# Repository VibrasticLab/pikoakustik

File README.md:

This is audiometri tool project (still in heavy development).
Main chip are STM32F401RE and Audio-DAC MAX98357A.

### Update:

After a year or so development struggle, now we move to some higher level development stage.
Therefor this repository will be archived and exist only for documentation.

Next development will be moved into new repository: [Pikoakustik2](https://github.com/VibrasticLab/pikoakustik2)

---

### Short Description:

- [x] Fungsional

Mengukur Ambang Pendengaran secara mandiri tanpa perlu bantuan dokter spesialis dan tanpa datang ke klinik.

- [x] Portabel

Dapat digunakan dimana saja dan kapan saja. Baterai mudah diisi ulang.

- [x] Terstandar

Telah terkalibrasi standar Audiometri dan teruji pada ruang *un-echoic*.

- [x] Ramah Pengguna

Antar Muka hanya berupa Tombol dan Lampu LED tanpa pengaturan tambahan dan bisa langsung digunakan.

- [x] Terintergrasi

Terhubung dengan penyimpanan *dedicated server* sehingga dapat diakses dokter spesialis secara jarak jauh jika diperlukan.

---

### Marking Rules:
- [ ] Unfinished
- [x] Finished but Open to Improve
- [x] ~~Finished~~
- [ ] ~~Unused but Noted~~

---

### Implemented Features:

#### User Interaction:

- [X] ~~LED Run Mode Indicator~~
	- [x] ~~Measurement Mode: Blink fast~~
	- [x] ~~Idle Mode: Blink slow~~
	- [x] ~~No Media Mode: Blink fast every 2s~~
- [X] ~~LED TRUE/FALSE~~
- [X] ~~LED Play/MMC~~
- [x] ~~LED 3 Choices~~
- [X] ~~Button Choices~~
	- [x] ~~3 Button Choices~~
	- [x] 3 Choices Random Generator
	- [x] ~~3 Choice Answer Placement~~
- [x] ~~Button Reset~~
- [x] ~~User-Friendlyness Interface Test~~
- [ ] LCD Non-Input Interface
	- [ ] LCD SPI ILI9xxx series

---

#### Packaging

- [x] ~~Acrilic Protector~~
- [ ] Box Design
	- [x] Print 3D
	- [ ] Plastic Molding
	- [x] Brosur Promo with Good Packaging
- [ ] Battery
	- [x] Regulator TP4056
	- [x] ~~LiPo Battery~~
	- [x] ~~Main Power Button~~
	- [ ] Charge/Discharge Test
	- [ ] Battery Manager
	- [x] No Cap except Run Elco

---

#### Data Communication:

- [ ] Serial Data
	- [x] ~~ACM USB-CDC Protocol~~
	- [x] ~~Basic Serial commands~~
	- [x] ~~Media handling commands~~
	- [x] ~~Audiometri control commands~~
	- [ ] HTTP Data control commands

- [x] ~~Media Storage~~
	- [x] ~~MMC Connector Slot~~
	- [x] ~~MMC readyness checking~~
	- [x] ~~FATFS as FAT32 handler~~
	- [x] ~~Via SPI protocol~~

- [ ] IoT Exchanges
	- [x] ESP-12E slot on PCB
	- [x] ESP-12E power jumper
	- [x] WiFi handling
	- [x] Access Point handling
	- [ ] Wifi/AP switch command
	- [ ] HTTP Data exchange
	- [ ] HTTP Data JSON/Format

---

#### Audiometri:

- [ ] Tone Generator
	- [x] ~~Generic I2S Protocol~~
	- [x] ~~Pure Single Tone~~
	- [x] Calibrated Frequency array
	- [x] Pop-Click Suppression
	- [x] Calibrated SPL range
	- [x] Calibrated SPL scaling
	- [x] Left/Right Isolation
	- [ ] Number Headphones
		- [ ] Embedded Tone Model
		- [ ] External Tone Model

- [ ] Hearing Test
	- [x] User Test Flow
	- [ ] **Convinient Level Test**
	- [ ] Random starting SPL
	- [x] Up/Down SPL scaling
	- [ ] Lowest Tone still too loud
	- [ ] Suffle Block
		- [ ] 1 Block is 1 Freq in 1 Channel
		- [ ] Left/Right suffle

- [ ] Microphone Input
	- [ ] Environment Noise Capture
	- [ ] Environment Noise Compensation

- [ ] Mass Production
	- [ ] PCB Electronic
		- [ ] Seeed Studio
		- [ ] ~~DigiKey~~
		- [ ] Xirca
		- [ ] Gerai-Cerdas
		- [ ] ~~Maxtron~~
	- [ ] Packaging

---

### Future Development:

- [ ] Migrate to ESP32
	- [ ] Advantage: Bluetooth Audio A2DP Sources
	- [ ] Advantage: Dual Core CPU as fast as ARM
	- [ ] Advantage: Touch Sensor (replace button)
	- [ ] Disadvantage: Less GPIO pin available
	- [ ] Disadvantage: Re-working all current design
	- [ ] Disadvantage: Re-calibrate and re-test everything

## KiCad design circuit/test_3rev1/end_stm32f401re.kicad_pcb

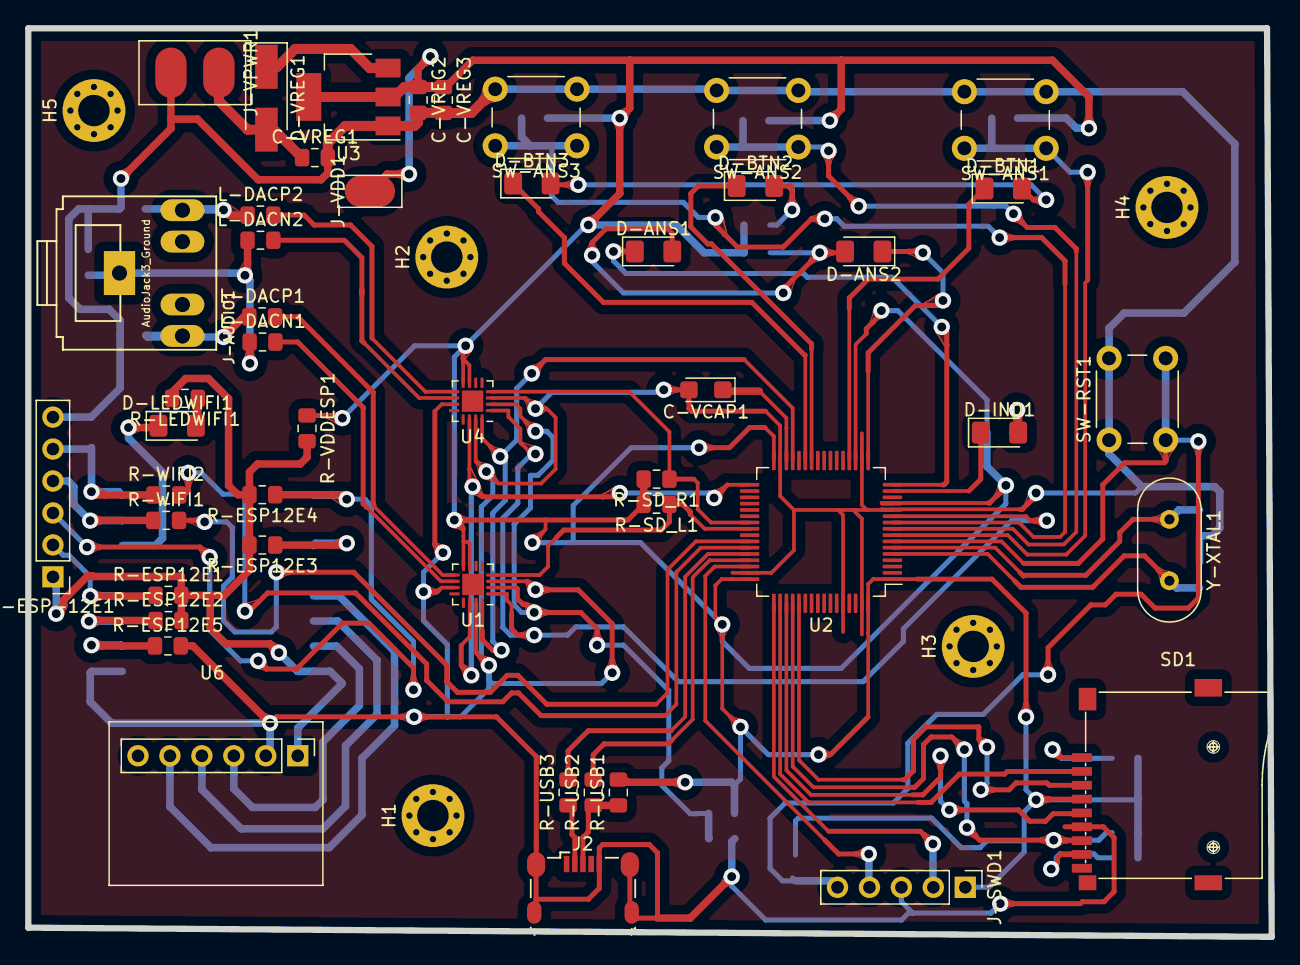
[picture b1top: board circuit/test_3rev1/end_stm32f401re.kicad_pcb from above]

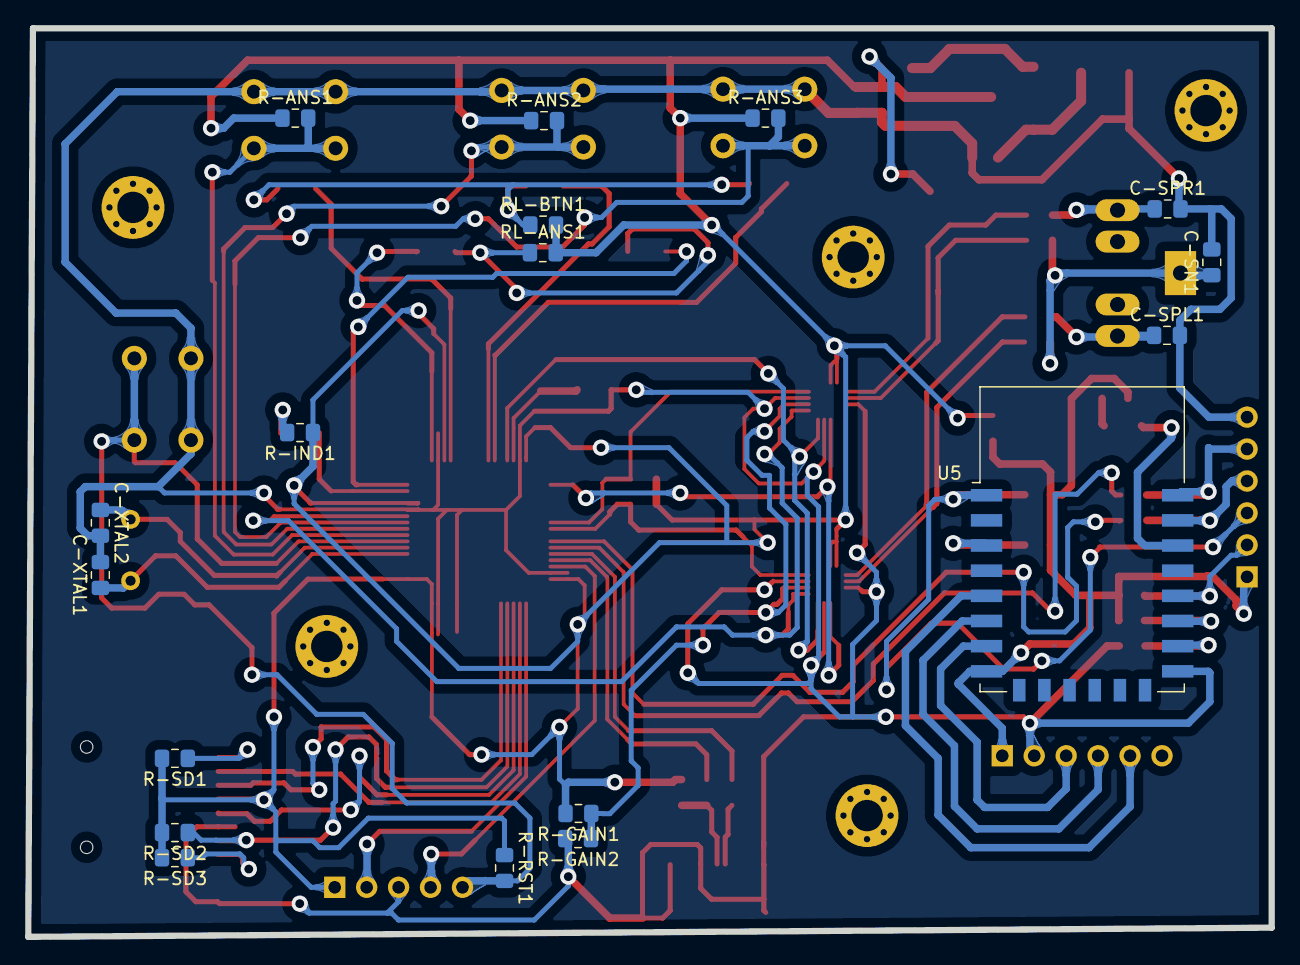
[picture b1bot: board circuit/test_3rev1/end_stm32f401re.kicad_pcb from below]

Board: 2 copper layers, 98.9 x 72.2 mm, 70 parts (18 on the bottom side), 60 nets.

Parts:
C-SN1: 220pF; C_0805_2012Metric_Pad1.15x1.40mm_HandSolder
C-SPL1: 220pF; C_0805_2012Metric_Pad1.15x1.40mm_HandSolder
C-SPR1: 220pF; C_0805_2012Metric_Pad1.15x1.40mm_HandSolder
C-VCAP1: 4.7uF; CP_EIA-3216-18_Kemet-A
C-VREG1, C-VREG2, C-VREG3: C; C_0805_2012Metric_Pad1.15x1.40mm_HandSolder
C-XTAL1, C-XTAL2: C; C_0805_2012Metric_Pad1.15x1.40mm_HandSolder
D-ANS1, D-ANS2: LED; LED_1206_3216Metric_Pad1.42x1.75mm_HandSolder
D-BTN1, D-BTN2, D-BTN3: LED; LED_1206_3216Metric_Pad1.42x1.75mm_HandSolder
D-IND1: LED; LED_1206_3216Metric_Pad1.42x1.75mm_HandSolder
D-LEDWIFI1: LED; LED_1206_3216Metric_Pad1.42x1.75mm_HandSolder
D-VREG1: D; D_SMA_Handsoldering
H1, H2, H3, H4: MountingHole; MountingHole_2.5mm_Pad_Via
H5: CableHole; MountingHole_2.5mm_Pad_Via
J2: USB_B_Micro; MicroUSB
J-AUDIO1: AudioJack3_Ground; Tayda_3.5mm_stereo_TRS_jack_A-853
J-ESP-12E1: Conn_01x06_Male; PinHeader_1x06_P2.54mm_Vertical
J-SWD1: Conn_01x05_Male; PinHeader_1x05_P2.54mm_Vertical
J-VDD1: Conn_01x01_Male; vpin-x1
J-VPWR1: Conn_01x02_Male; vpin-x2
L-DACN1, L-DACN2: 100uH; L_0805_2012Metric_Pad1.15x1.40mm_HandSolder
L-DACP1, L-DACP2: 100uH; L_0805_2012Metric_Pad1.15x1.40mm_HandSolder
R-ANS1, R-ANS2, R-ANS3: 10K; R_0805_2012Metric_Pad1.15x1.40mm_HandSolder
R-ESP12E1, R-ESP12E2, R-ESP12E3, R-ESP12E4, R-ESP12E5: 10K; R_0805_2012Metric_Pad1.15x1.40mm_HandSolder
R-GAIN1, R-GAIN2: 100K; R_0805_2012Metric_Pad1.15x1.40mm_HandSolder
R-IND1: 330; R_0805_2012Metric_Pad1.15x1.40mm_HandSolder
R-LEDWIFI1: 330; R_0805_2012Metric_Pad1.15x1.40mm_HandSolder
R-RST1: 10K; R_0805_2012Metric_Pad1.15x1.40mm_HandSolder
R-SD1, R-SD2, R-SD3: 10K; R_0805_2012Metric_Pad1.15x1.40mm_HandSolder
R-SD_L1: 1M; R_0805_2012Metric_Pad1.15x1.40mm_HandSolder
R-SD_R1: 1M; R_0805_2012Metric_Pad1.15x1.40mm_HandSolder
R-USB1: 4K7; R_0805_2012Metric_Pad1.15x1.40mm_HandSolder
R-USB2, R-USB3: 68; R_0805_2012Metric_Pad1.15x1.40mm_HandSolder
R-VDDESP1: 0; R_0805_2012Metric_Pad1.15x1.40mm_HandSolder
R-WIFI1, R-WIFI2: 0; R_0805_2012Metric_Pad1.15x1.40mm_HandSolder
RL-ANS1: 330; R_0805_2012Metric_Pad1.15x1.40mm_HandSolder
RL-BTN1: 330; R_0805_2012Metric_Pad1.15x1.40mm_HandSolder
SD1: MICRO-SD-CARD-SOCKET-9P_ST-TF-003A_; MICRO-SD9+4P-SMD-16.1X14.5X1.85MM
SW-ANS1, SW-ANS2, SW-ANS3: SW_Push; SW_PUSH_6mm
SW-RST1: SW_Push; SW_PUSH_6mm
U1, U4: MAX98357; QFN-16-1EP_3x3mm_P0.5mm_EP1.7x1.7mm
U2: STM32F401RETx; LQFP-64_10x10mm_P0.5mm
U3: AMS1117-3.3; SOT-223-3_TabPin2
U5: ESP-12E
U6: SPH0645; sph0645
Y-XTAL1: 16MHz; Crystal_HC49-4H_Vertical

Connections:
/BTN_A: R-ANS1.2, SW-ANS1.1, U2.8
/BTN_B: R-ANS2.2, SW-ANS2.1, U2.9
/BTN_C: R-ANS3.2, SW-ANS3.1, U2.10
/DAC_BCLK: U1.16, U2.29, U4.16
/DAC_DIN: U1.1, U2.11, U4.1
/DAC_GAIN: R-GAIN1.1, R-GAIN2.1, U1.2, U4.2
/DAC_LRC: U1.14, U2.33, U4.14
/DAC_L_SD: R-SD_L1.1, U1.4, U2.40
/DAC_R_SD: R-SD_R1.1, U2.39, U4.4
/ESP_EN: R-ESP12E3.1, U5.3
/ESP_LEDWIFI: D-LEDWIFI1.1, U5.20
/ESP_P0: J-ESP-12E1.2, R-ESP12E1.1, U5.18
/ESP_P2: R-ESP12E2.1, U5.17
/ESP_P15: R-ESP12E5.1, U5.16
/ESP_RST: J-ESP-12E1.3, R-ESP12E4.1, U5.1
/ESP_RXD: J-ESP-12E1.4, R-WIFI1.1, U5.21
/ESP_TXD: J-ESP-12E1.5, R-WIFI2.1, U5.22
/LED_A: D-BTN1.1, U2.20
/LED_B: D-BTN2.1, U2.26
/LED_C: D-BTN3.1, U2.27
/LED_FALSE: D-ANS2.1, U2.17
/LED_IND: D-IND1.1, U2.15
/LED_TRUE: D-ANS1.1, U2.16
/MIC_BCLK: U5.7, U6.3
/MIC_DOUT: U5.6, U6.4
/MIC_LRCL: U5.5, U6.5
/MMC_MISO: R-SD2.1, SD1.7, U2.52
/MMC_MOSI: SD1.3, U2.53
/MMC_NSS: SD1.2, U2.50
/MMC_SCK: SD1.5, U2.51
/NRST: J-SWD1.5, R-RST1.2, SW-RST1.2, U2.7
/OUTN: C-SN1.1, J-AUDIO1.S, L-DACN1.1, L-DACN2.1
/OUTP_L: C-SPL1.1, J-AUDIO1.T, L-DACP1.1
/OUTP_R: C-SPR1.1, J-AUDIO1.R, L-DACP2.1
/SW_CLK: J-SWD1.2, U2.49
/SW_DIO: J-SWD1.4, U2.46
/USB_DM: R-USB3.2, U2.44
/USB_DP: R-USB2.2, U2.45
/VDD-ESP8266: J-ESP-12E1.1, R-ESP12E1.2, R-ESP12E2.2, R-ESP12E3.2, R-ESP12E4.2, R-LEDWIFI1.2, R-VDDESP1.2, U5.8, U6.1
/WIFI_RXD: R-WIFI2.2, U2.43
/WIFI_TXD: R-WIFI1.2, U2.42
GND: C-SN1.2, C-SPL1.2, C-SPR1.2, C-VCAP1.2, C-VREG1.2, C-VREG2.2, C-VREG3.2, C-XTAL1.2, C-XTAL2.2, J2.5, J2.6, J-ESP-12E1.6, J-SWD1.3, J-VPWR1.2, R-ESP12E5.2, R-GAIN2.2, SD1.6, SW-ANS1.2, SW-ANS2.2, SW-ANS3.2, SW-RST1.1, U1.3, U1.11, U1.15, U2.12, U2.18, U2.31, U2.47, U2.60, U2.63, U3.1, U4.3, U4.11, U4.15, U5.15, U6.2
unnamed: C-VCAP1.1, U2.30
unnamed: C-XTAL1.1, U2.5, Y-XTAL1.2
unnamed: C-XTAL2.1, U2.6, Y-XTAL1.1
unnamed: D-ANS1.2, D-ANS2.2, RL-ANS1.1
unnamed: D-BTN1.2, D-BTN2.2, D-BTN3.2, RL-BTN1.1
unnamed: D-IND1.2, R-IND1.2
unnamed: D-LEDWIFI1.2, R-LEDWIFI1.1
unnamed: D-VREG1.1, U3.3
unnamed: J2.2, R-USB3.1
unnamed: J2.3, R-USB1.1, R-USB2.1
unnamed: L-DACN1.2, U1.10
unnamed: L-DACN2.2, U4.10
unnamed: L-DACP1.2, U1.9
unnamed: L-DACP2.2, U4.9
unnamed: R-SD1.1, SD1.1
unnamed: R-SD3.1, SD1.8
VCC: C-VREG1.1, D-VREG1.2, J-VPWR1.1
VDD: C-VREG2.1, C-VREG3.1, J-SWD1.1, J-VDD1.1, R-ANS1.1, R-ANS2.1, R-ANS3.1, R-GAIN1.2, R-IND1.1, R-RST1.1, R-SD1.2, R-SD2.2, R-SD3.2, R-SD_L1.2, R-SD_R1.2, R-USB1.2, R-VDDESP1.1, RL-ANS1.2, RL-BTN1.2, SD1.4, U1.7, U1.8, U2.1, U2.13, U2.19, U2.32, U2.48, U2.64, U3.2, U4.7, U4.8

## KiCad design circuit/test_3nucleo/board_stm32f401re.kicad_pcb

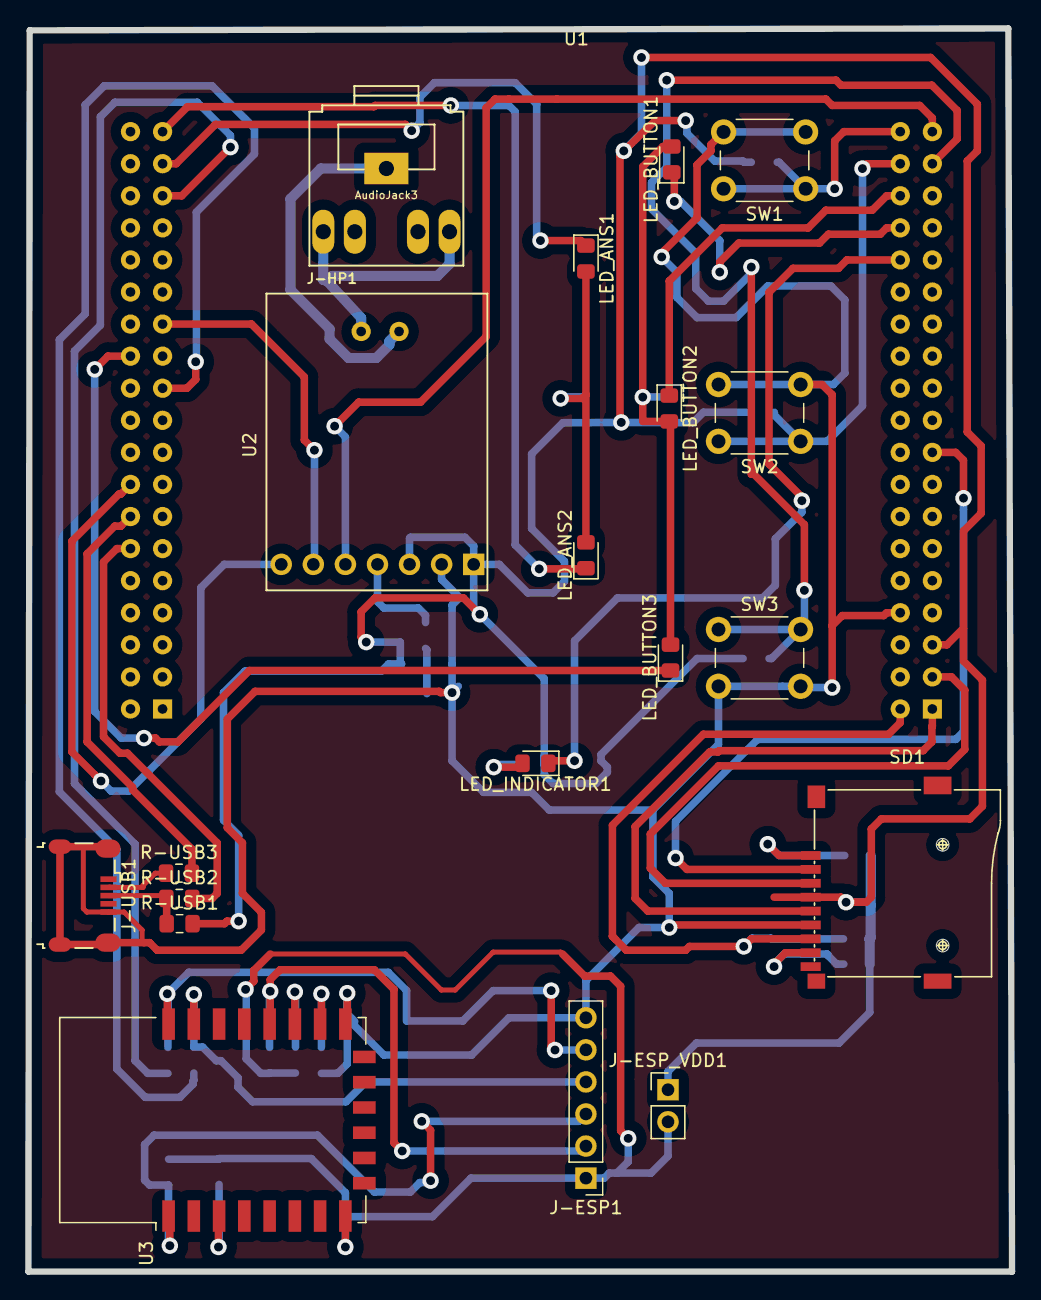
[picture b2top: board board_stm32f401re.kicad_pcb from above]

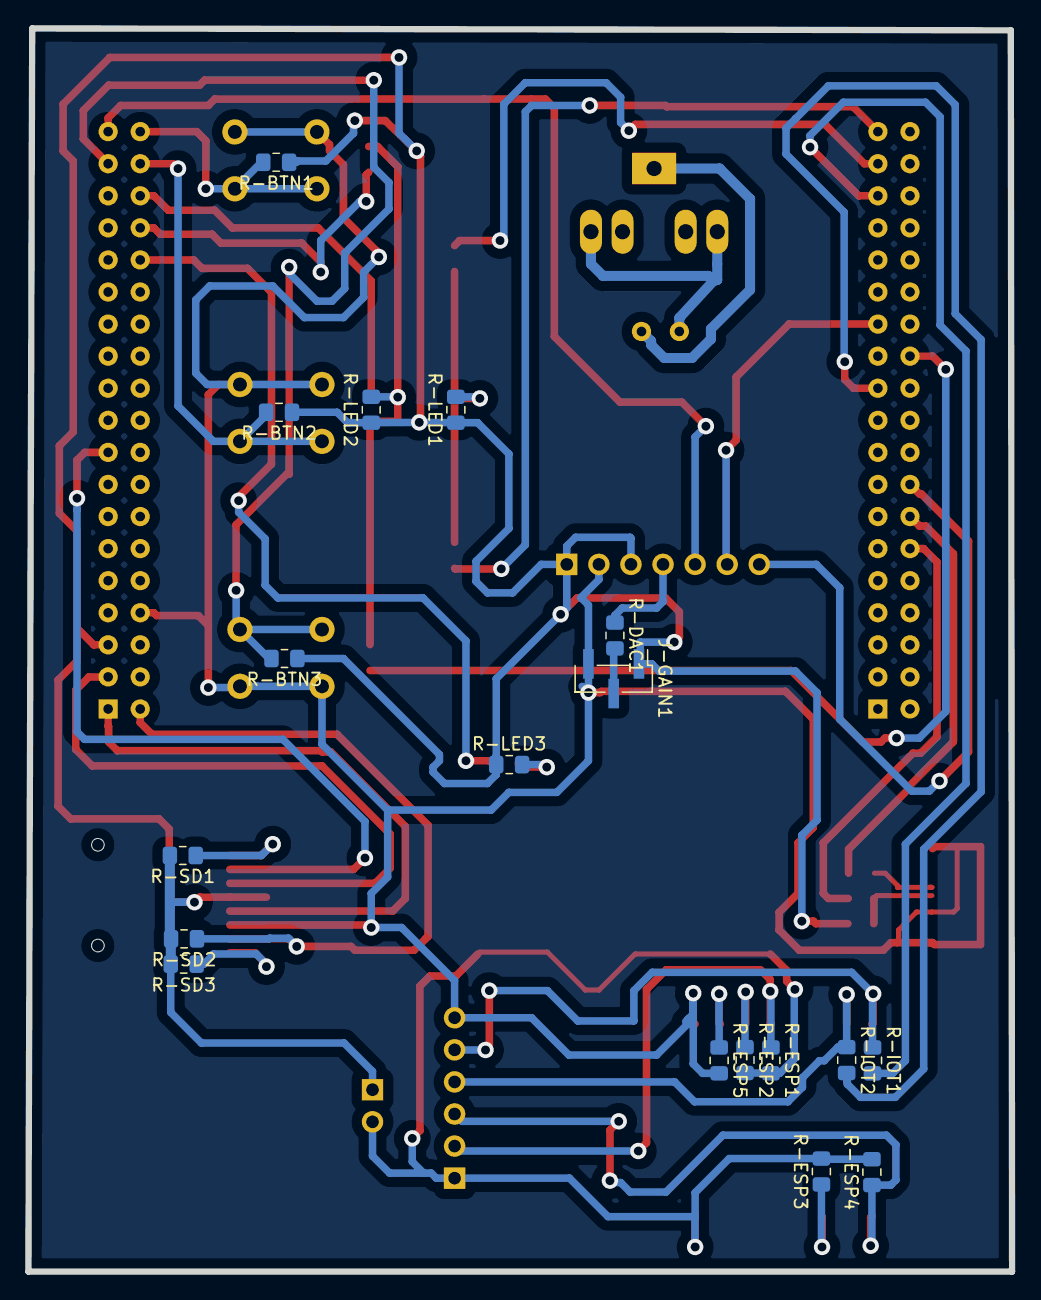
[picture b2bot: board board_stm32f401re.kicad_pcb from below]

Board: 2 copper layers, 77.9 x 98.5 mm, 38 parts (18 on the bottom side), 41 nets.

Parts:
J-ESP1: Conn_01x06_Male; PinHeader_1x06_P2.54mm_Vertical
J-ESP_VDD1: Conn_01x02_Male; PinHeader_1x02_P2.54mm_Vertical
J-GAIN1: Conn_01x03_Male; PinHeader_1x03_P2.00mm_Vertical_SMD_Pin1Left
J-HP1: AudioJack3; Tayda_3.5mm_stereo_TRS_jack_A-853
J-USB1: USB_B_Micro; MicroUSB
LED_ANS1, LED_ANS2: LED; LED_0805_2012Metric_Pad1.15x1.40mm_HandSolder
LED_BUTTON1, LED_BUTTON2, LED_BUTTON3: LED; LED_0805_2012Metric_Pad1.15x1.40mm_HandSolder
LED_INDICATOR1: LED; LED_0805_2012Metric_Pad1.15x1.40mm_HandSolder
R-BTN1, R-BTN2, R-BTN3: 4K7; R_0805_2012Metric_Pad1.15x1.40mm_HandSolder
R-DAC1: 100K; R_0805_2012Metric_Pad1.15x1.40mm_HandSolder
R-ESP1, R-ESP2, R-ESP3, R-ESP4, R-ESP5: 4K7; R_0805_2012Metric_Pad1.15x1.40mm_HandSolder
R-IOT1, R-IOT2: 0; R_0805_2012Metric_Pad1.15x1.40mm_HandSolder
R-LED1, R-LED2, R-LED3: 330; R_0805_2012Metric_Pad1.15x1.40mm_HandSolder
R-SD1, R-SD2, R-SD3: 4K7; R_0805_2012Metric_Pad1.15x1.40mm_HandSolder
R-USB1: 4K7; R_0805_2012Metric_Pad1.15x1.40mm_HandSolder
R-USB2, R-USB3: 68; R_0805_2012Metric_Pad1.15x1.40mm_HandSolder
SD1: MICRO-SD-CARD-SOCKET-9P_ST-TF-003A_; MICRO-SD9+4P-SMD-16.1X14.5X1.85MM
SW1, SW2, SW3: SW_Push; SW_PUSH_6mm
U1: NUCLEO-64; Nucleo-64
U2: MAX98357_DAC; dacmax98357
U3: ESP-12E

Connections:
/BTN_A: R-BTN1.2, SW1.1, U1.38
/BTN_B: R-BTN2.2, SW2.1, U1.36
/BTN_C: R-BTN3.2, SW3.1, U1.35
/DAC_BCLK: U1.63, U2.6
/DAC_DIN: U1.37, U2.5
/DAC_LRC: U1.54, U2.7
/ESP_EN: R-ESP3.1, U3.3
/ESP_P0: J-ESP1.2, R-ESP1.1, U3.18
/ESP_P2: R-ESP2.1, U3.17
/ESP_P15: R-ESP5.1, U3.16
/ESP_RST: J-ESP1.3, R-ESP4.1, U3.1
/ESP_RXD: J-ESP1.4, R-IOT2.1, U3.21
/ESP_TXD: J-ESP1.5, R-IOT1.1, U3.22
/ESP_VDD: J-ESP1.1, J-ESP_VDD1.2, R-ESP1.2, R-ESP2.2, R-ESP3.2, R-ESP4.2, U3.8
/LED_A: LED_BUTTON1.1, U1.32
/LED_B: LED_BUTTON2.1, U1.34
/LED_C: LED_BUTTON3.1, U1.62
/LED_FALSE: LED_ANS2.1, U1.75
/LED_IND: LED_INDICATOR1.1, U1.30
/LED_TRUE: LED_ANS1.1, U1.73
/MMC_MISO: R-SD2.1, SD1.7, U1.2
/MMC_MOSI: SD1.3, U1.3
/MMC_NSS: SD1.2, U1.17
/MMC_SCK: SD1.5, U1.1
/RXD: R-IOT1.2, U1.71
/TXD: R-IOT2.2, U1.59
/USB_DM: R-USB3.2, U1.52
/USB_DP: R-USB2.2, U1.50
GND: J-ESP1.6, J-GAIN1.3, J-USB1.5, J-USB1.6, R-ESP5.2, SD1.6, SW1.2, SW2.2, SW3.2, U1.8, U2.2, U3.15
unnamed: J-GAIN1.2, R-DAC1.2
unnamed: J-HP1.R, J-HP1.T, U2.9
unnamed: J-HP1.S, U2.8
unnamed: J-USB1.2, R-USB3.1
unnamed: J-USB1.3, R-USB1.1, R-USB2.1
unnamed: LED_ANS1.2, LED_ANS2.2, R-LED1.2
unnamed: LED_BUTTON1.2, LED_BUTTON2.2, LED_BUTTON3.2, R-LED2.2
unnamed: LED_INDICATOR1.2, R-LED3.2
unnamed: R-DAC1.1, U2.4
unnamed: R-SD1.1, SD1.1
unnamed: R-SD3.1, SD1.8
VDD: J-ESP_VDD1.1, J-GAIN1.1, R-BTN1.1, R-BTN2.1, R-BTN3.1, R-LED1.1, R-LED2.1, R-LED3.1, R-SD1.2, R-SD2.2, R-SD3.2, R-USB1.2, SD1.4, U1.5, U2.1, U2.3

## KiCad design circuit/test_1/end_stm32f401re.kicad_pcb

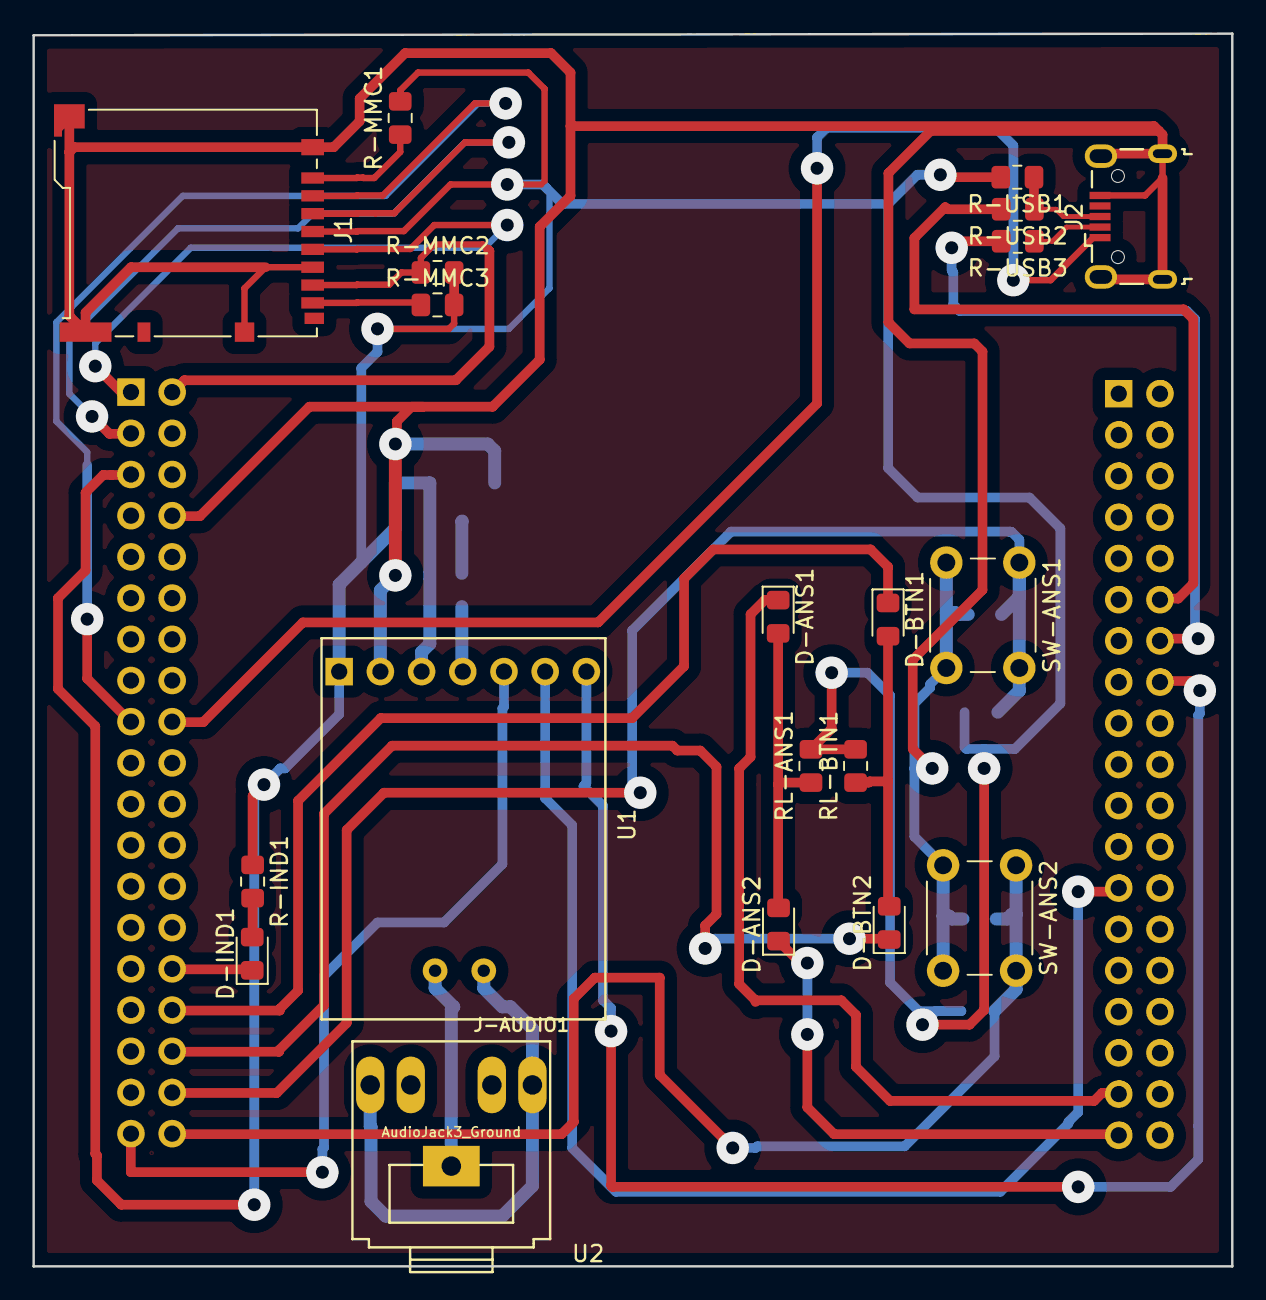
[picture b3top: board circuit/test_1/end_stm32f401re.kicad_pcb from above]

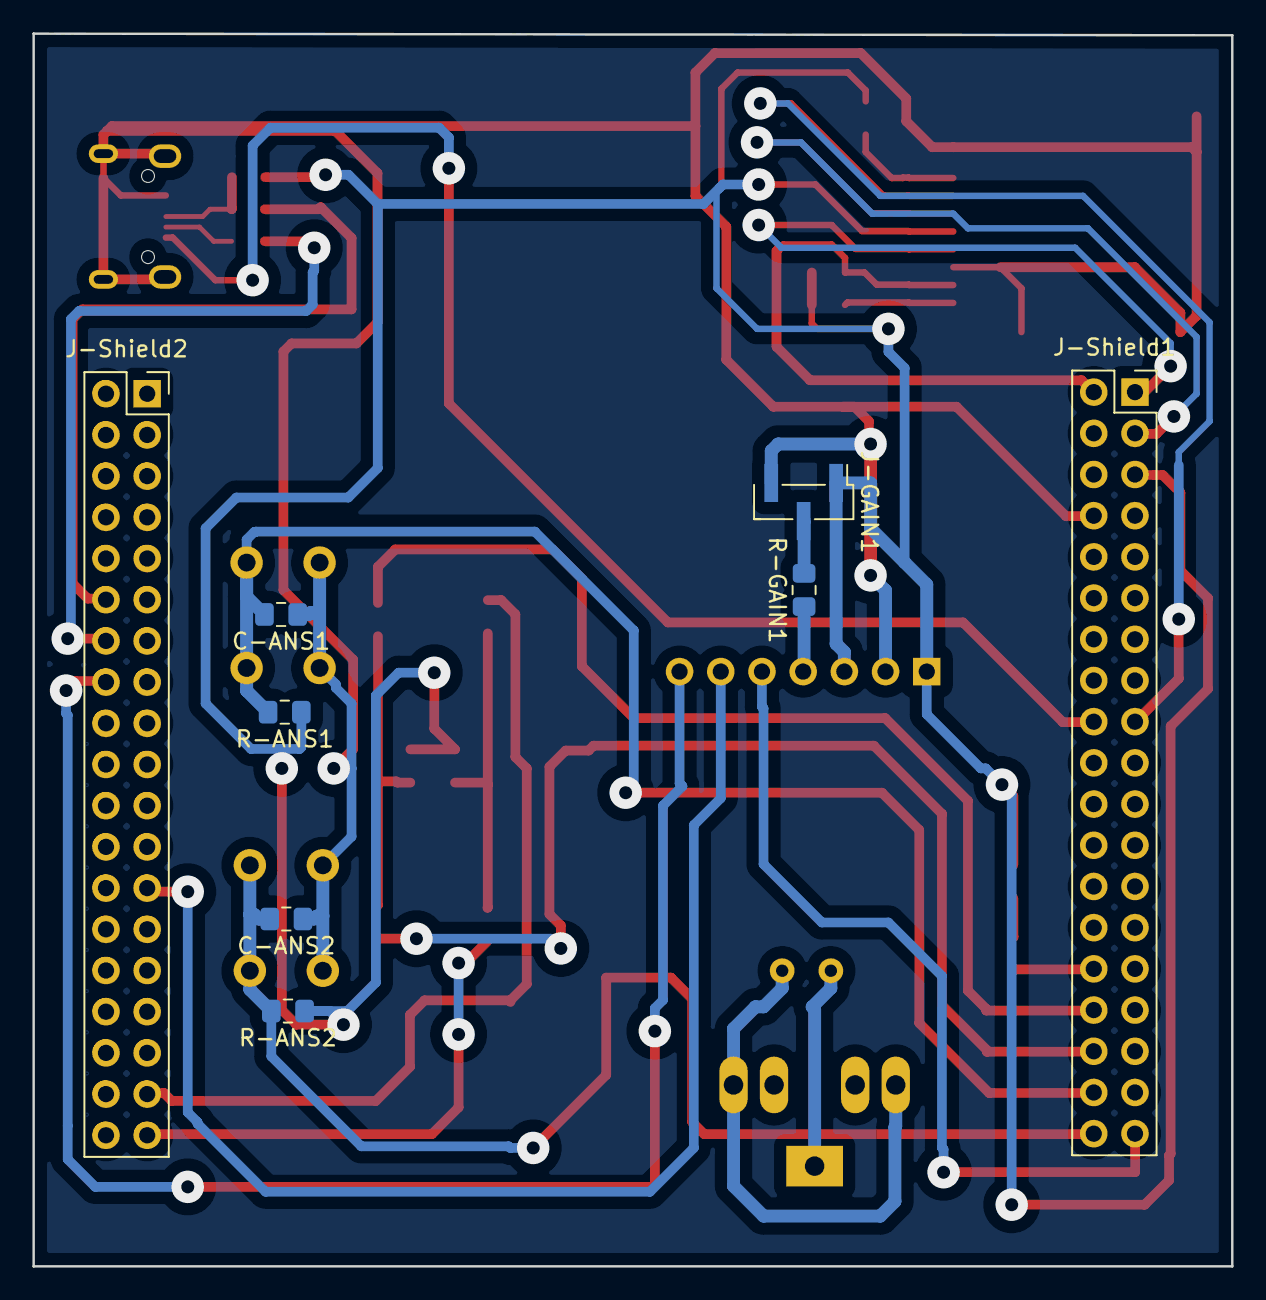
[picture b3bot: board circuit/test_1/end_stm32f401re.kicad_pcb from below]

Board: 2 copper layers, 73.9 x 76.0 mm, 29 parts (8 on the bottom side), 30 nets.

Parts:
C-ANS1, C-ANS2: C; C_0805_2012Metric_Pad1.15x1.40mm_HandSolder
D-ANS1, D-ANS2: LED; LED_0805_2012Metric_Pad1.15x1.40mm_HandSolder
D-BTN1, D-BTN2: LED; LED_0805_2012Metric_Pad1.15x1.40mm_HandSolder
D-IND1: LED; LED_0805_2012Metric_Pad1.15x1.40mm_HandSolder
J1: Micro_SD_Card_Det; microSD_HC_Hirose_DM3BT-DSF-PEJS
J2: USB_B_Micro; USB_Micro-B_Wuerth_629105150521
J-AUDIO1: AudioJack3_Ground; Tayda_3.5mm_stereo_TRS_jack_A-853
J-GAIN1: Conn_01x03_Male; PinHeader_1x03_P2.00mm_Vertical_SMD_Pin1Left
J-Shield1, J-Shield2: Conn_02x19_Odd_Even; PinSocket_2x19_P2.54mm_Vertical
R-ANS1, R-ANS2: 10K; R_0805_2012Metric_Pad1.15x1.40mm_HandSolder
R-GAIN1: 100K; R_0805_2012Metric_Pad1.15x1.40mm_HandSolder
R-IND1: 330; R_0805_2012Metric_Pad1.15x1.40mm_HandSolder
R-MMC1, R-MMC2, R-MMC3: 10K; R_0805_2012Metric_Pad1.15x1.40mm_HandSolder
R-USB1: 4K7; R_0805_2012Metric_Pad1.15x1.40mm_HandSolder
R-USB2, R-USB3: 68; R_0805_2012Metric_Pad1.15x1.40mm_HandSolder
RL-ANS1: 330; R_0805_2012Metric_Pad1.15x1.40mm_HandSolder
RL-BTN1: 330; R_0805_2012Metric_Pad1.15x1.40mm_HandSolder
SW-ANS1, SW-ANS2: SW_Push; SW_PUSH_6mm
U1: MAX98357_DAC; dacmax98357
U2: NUCLEO-64; Nucleo-64

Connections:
/BTN_A: C-ANS1.2, R-ANS1.2, SW-ANS1.1, U2.36
/BTN_B: C-ANS2.2, R-ANS2.2, SW-ANS2.1, U2.38
/DAC_BCLK: U1.6, U2.63
/DAC_DIN: U1.5, U2.37
/DAC_LRC: U1.7, U2.54
/LED_A: D-BTN1.1, U2.32
/LED_B: D-BTN2.1, U2.34
/LED_FALSE: D-ANS2.1, U2.75
/LED_IND: D-IND1.1, U2.30
/LED_TRUE: D-ANS1.1, U2.73
/MMC_MISO: J1.7, R-MMC2.1, U2.2
/MMC_MOSI: J1.3, U2.3
/MMC_NSS: J1.2, U2.17
/MMC_SCK: J1.5, U2.1
/USB_DM: R-USB3.2, U2.52
/USB_DP: R-USB2.2, U2.50
GND: C-ANS1.1, C-ANS2.1, J1.6, J1.11, J2.5, J2.6, J-GAIN1.3, SW-ANS1.2, SW-ANS2.2, U1.2, U2.8
unnamed: D-ANS1.2, D-ANS2.2, RL-ANS1.1
unnamed: D-BTN1.2, D-BTN2.2, RL-BTN1.1
unnamed: D-IND1.2, R-IND1.2
unnamed: J1.1, R-MMC1.1
unnamed: J1.8, R-MMC3.1
unnamed: J2.2, R-USB3.1
unnamed: J2.3, R-USB1.1, R-USB2.1
unnamed: J-AUDIO1.R, J-AUDIO1.T, U1.9
unnamed: J-AUDIO1.S, U1.8
unnamed: J-GAIN1.2, R-GAIN1.2
unnamed: R-GAIN1.1, U1.4
VCC: J2.1, U2.18
VDD: J1.4, J-GAIN1.1, R-ANS1.1, R-ANS2.1, R-IND1.1, R-MMC1.2, R-MMC2.2, R-MMC3.2, R-USB1.2, RL-ANS1.2, RL-BTN1.2, U1.1, U1.3, U2.5

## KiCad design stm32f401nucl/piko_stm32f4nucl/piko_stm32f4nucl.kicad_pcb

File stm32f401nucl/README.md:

This platform is for STM32F401RE Nucleo board.

Software Requirement:
- arm-none-eabi GCC toolchain
- GNU/Make
- ChibiOS/RT version 3.x
- stlink or stm32flash

on Arch Linux, install using command:
~~~
sudo pacman -S arm-none-eabi-gcc arm-none-eabi-newlib stlink
~~~

Hardware Requirement:
- STM32F401RE Nucleo board.
- Audio DAC using I2S interface (e.g MAX98357A)
- Micro SDCard
- Led Indicator
- Push Button

Connection:
- Audio DAC
~~~
STM32	MAX98
----	----
GND		GND
VDD		Vin
VDD		SD (Shutdown)
PC3		Din (Data)
PB10	BCLK
PB12	LRC
~~~
- MicroSDCard
STM32	SDCard
----	----
GND		VSS
VDD		VDD
VDD		DAT2 (10k pullup)
PA4		NSS/DAT3/CD
PA7		MOSI
PA5		CLK
PA6		MISO/DAT0 (10k pullup)
VDD		DAT1 (10k pullup)
~~~

For the record, there's range on:
- Frequency: from 500 to 10000 (not calibrated in Hz)
- Amplitudo: from 10 to 10000 (not calibrated in dB)

To build, just run on top repos directory:
~~~
./build.sh stm32f401nucl
~~~

If no error on compiling, connect board to usb then run:
~~~
sudo st-flash write build/stm32f401nucl/build/pikotes.bin 0x8000000
~~~

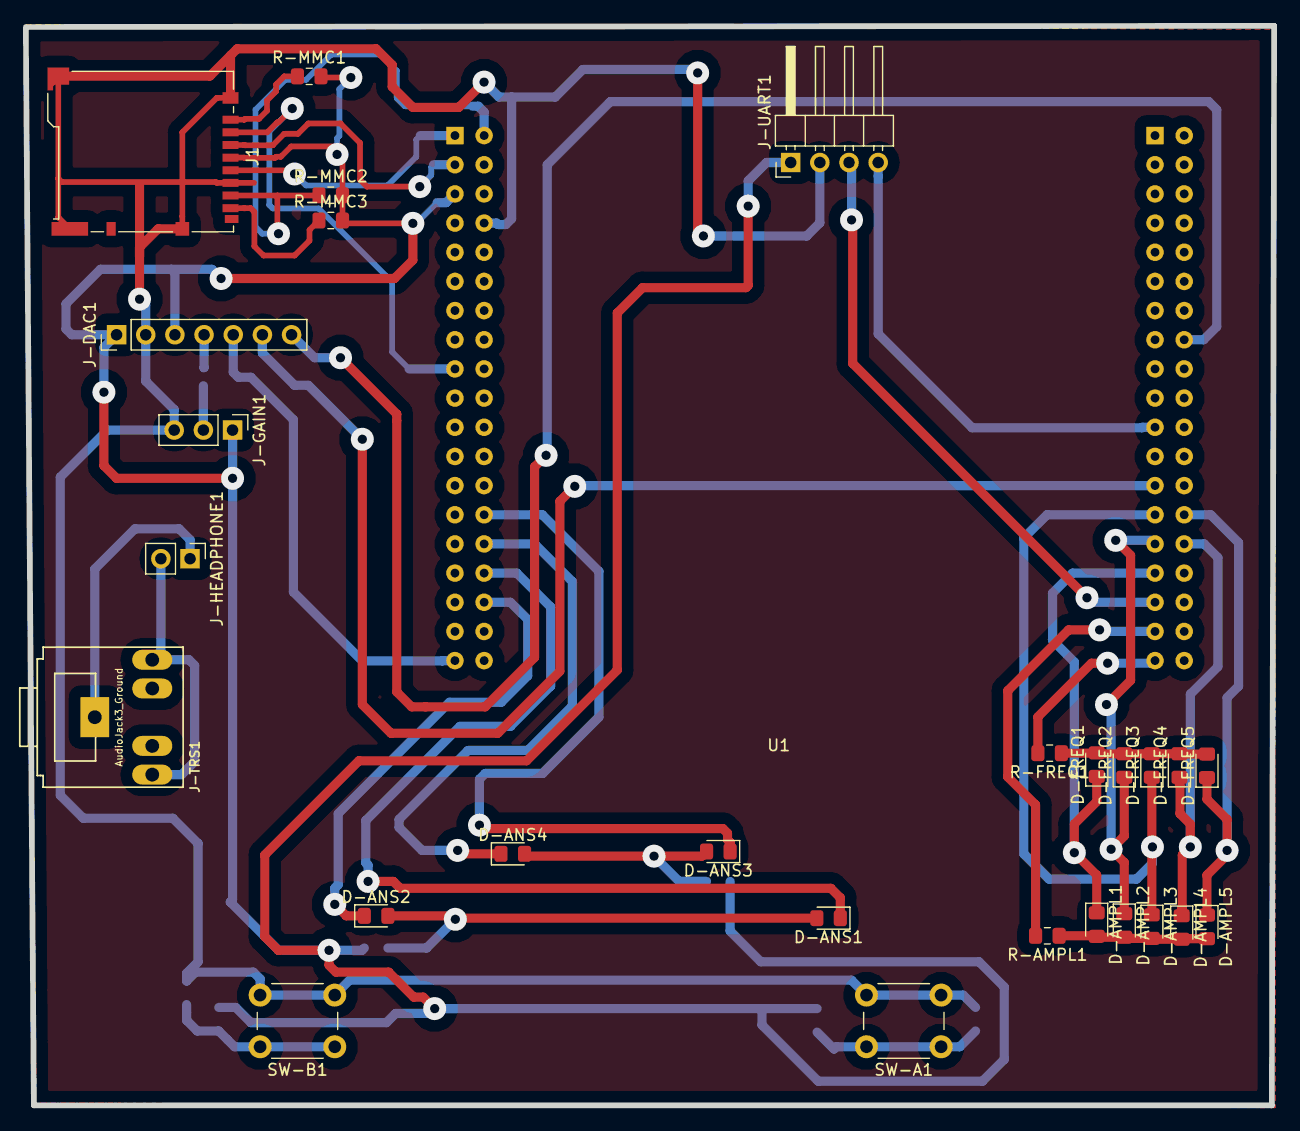
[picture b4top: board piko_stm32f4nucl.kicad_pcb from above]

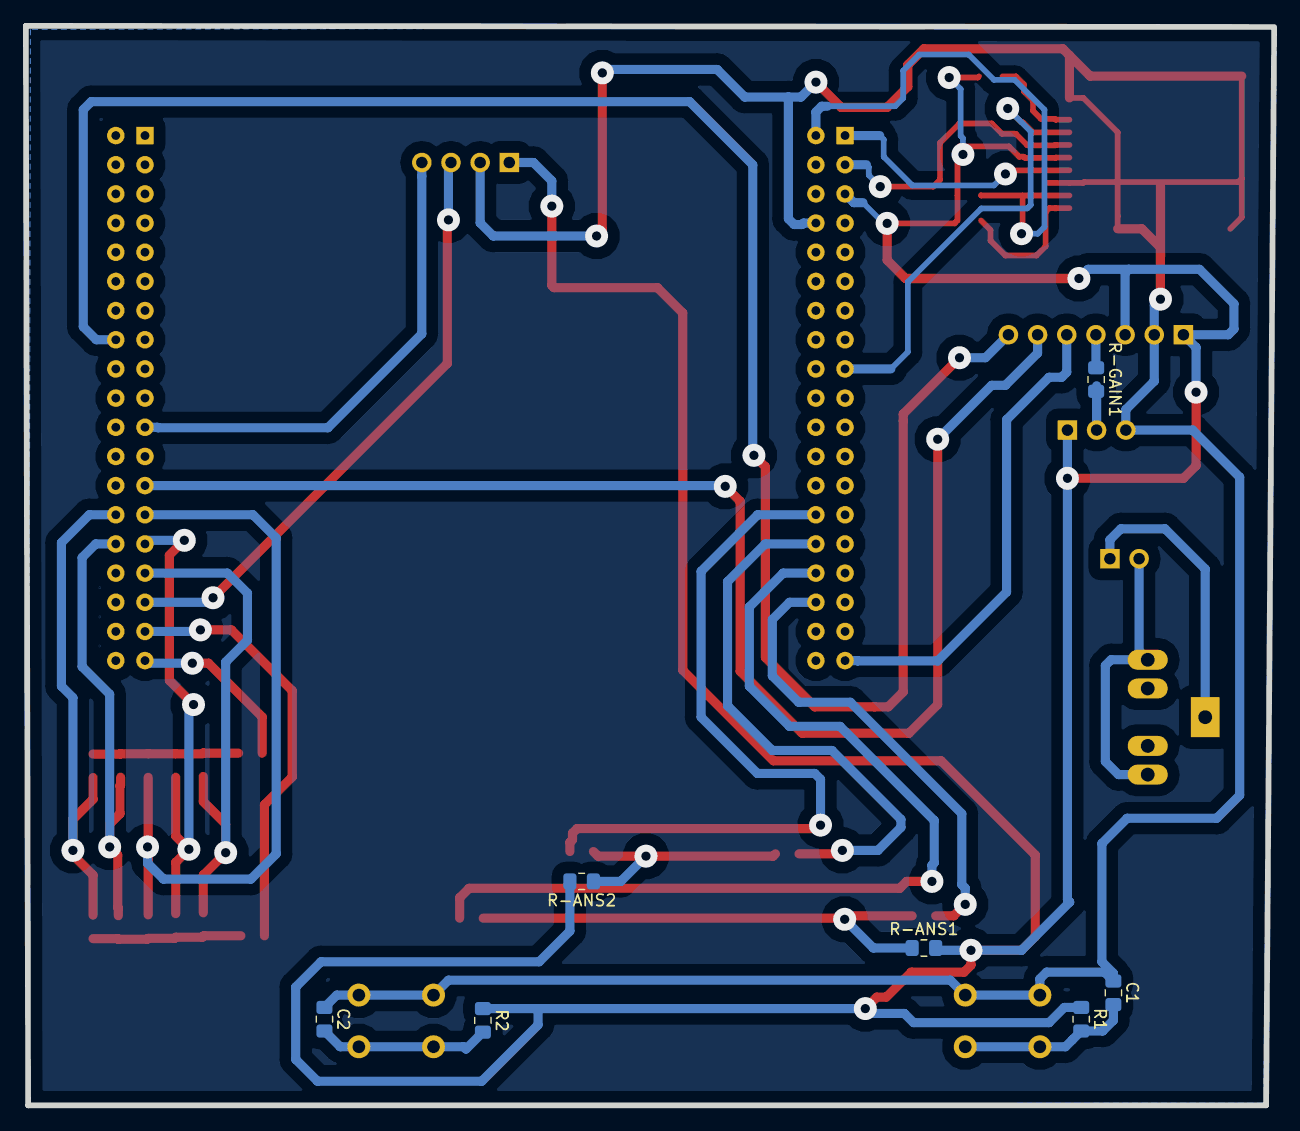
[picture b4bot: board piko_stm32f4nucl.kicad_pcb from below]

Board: 2 copper layers, 108.7 x 94.0 mm, 35 parts (7 on the bottom side), 34 nets.

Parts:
C1, C2: C; C_0805_2012Metric_Pad1.15x1.40mm_HandSolder
D-AMPL1, D-AMPL2, D-AMPL3, D-AMPL4, D-AMPL5: LED; LED_0805_2012Metric_Pad1.15x1.40mm_HandSolder
D-ANS1, D-ANS2, D-ANS3, D-ANS4: LED; LED_0805_2012Metric_Pad1.15x1.40mm_HandSolder
D-FREQ1, D-FREQ2, D-FREQ3, D-FREQ4, D-FREQ5: LED; LED_0805_2012Metric_Pad1.15x1.40mm_HandSolder
J1: Micro_SD_Card_Det; microSD_HC_Hirose_DM3BT-DSF-PEJS
J-DAC1: Conn_01x07_Female; PinHeader_1x07_P2.54mm_Vertical
J-GAIN1: Conn_01x03_Male; PinHeader_1x03_P2.54mm_Vertical
J-HEADPHONE1: Conn_01x02_Female; PinHeader_1x02_P2.54mm_Vertical
J-TRS1: AudioJack3_Ground; Tayda_3.5mm_stereo_TRS_jack_A-853
J-UART1: Conn_01x04_Male; PinHeader_1x04_P2.54mm_Horizontal
R1, R2: 4k7; R_0805_2012Metric_Pad1.15x1.40mm_HandSolder
R-AMPL1: 100; R_0805_2012Metric_Pad1.15x1.40mm_HandSolder
R-ANS1, R-ANS2: 300; R_0805_2012Metric_Pad1.15x1.40mm_HandSolder
R-FREQ1: 100; R_0805_2012Metric_Pad1.15x1.40mm_HandSolder
R-GAIN1: R; R_0805_2012Metric_Pad1.15x1.40mm_HandSolder
R-MMC1, R-MMC2, R-MMC3: 10k; R_0805_2012Metric_Pad1.15x1.40mm_HandSolder
SW-A1: SW_Push; SW_PUSH_6mm
SW-B1: SW_Push; SW_PUSH_6mm
U1: NUCLEO-64; Nucleo-64

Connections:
/BCLK: J-DAC1.6, U1.63
/DATA: J-DAC1.5, U1.37
/GAIN: J-DAC1.4, R-GAIN1.1
/HP_M: J-HEADPHONE1.1, J-TRS1.S
/HP_P: J-HEADPHONE1.2, J-TRS1.R, J-TRS1.T
/LED_AMPL: R-AMPL1.2, U1.73
/LED_ANS_A: D-ANS1.1, U1.32
/LED_ANS_B: D-ANS2.1, U1.34
/LED_ANS_FALSE: D-ANS4.1, U1.30
/LED_ANS_TRUE: D-ANS3.1, U1.28
/LED_FREQ: R-FREQ1.2, U1.75
/LED_M1: D-AMPL1.1, D-FREQ1.1, U1.69
/LED_M2: D-AMPL2.1, D-FREQ2.1, U1.67
/LED_M3: D-AMPL3.1, D-FREQ3.1, U1.65
/LED_M4: D-AMPL4.1, D-FREQ4.1, U1.68
/LED_M5: D-AMPL5.1, D-FREQ5.1, U1.66
/LRC: J-DAC1.7, U1.54
/MMC_MISO: J1.7, R-MMC2.1, U1.2
/MMC_MOSI: J1.3, U1.3
/MMC_NSS: J1.2, U1.17
/MMC_SCK: J1.5, U1.1
/RX: J-UART1.3, U1.71
/TX: J-UART1.4, U1.59
GND: C1.1, C2.1, J1.6, J1.11, J-DAC1.2, J-GAIN1.3, J-UART1.2, SW-A1.2, SW-B1.2, U1.8
unnamed: C1.2, R1.2, SW-B1.1
unnamed: C2.2, R2.2, SW-A1.1
unnamed: D-AMPL1.2, D-AMPL2.2, D-AMPL3.2, D-AMPL4.2, D-AMPL5.2, R-AMPL1.1
unnamed: D-ANS1.2, D-ANS2.2, R-ANS1.1
unnamed: D-ANS3.2, D-ANS4.2, R-ANS2.1
unnamed: D-FREQ1.2, D-FREQ2.2, D-FREQ3.2, D-FREQ4.2, D-FREQ5.2, R-FREQ1.1
unnamed: J1.1, R-MMC1.1
unnamed: J1.8, R-MMC3.1
unnamed: J-GAIN1.2, R-GAIN1.2
VDD: J1.4, J-DAC1.1, J-DAC1.3, J-GAIN1.1, J-UART1.1, R1.1, R2.1, R-ANS1.2, R-ANS2.2, R-MMC1.2, R-MMC2.2, R-MMC3.2, U1.5
